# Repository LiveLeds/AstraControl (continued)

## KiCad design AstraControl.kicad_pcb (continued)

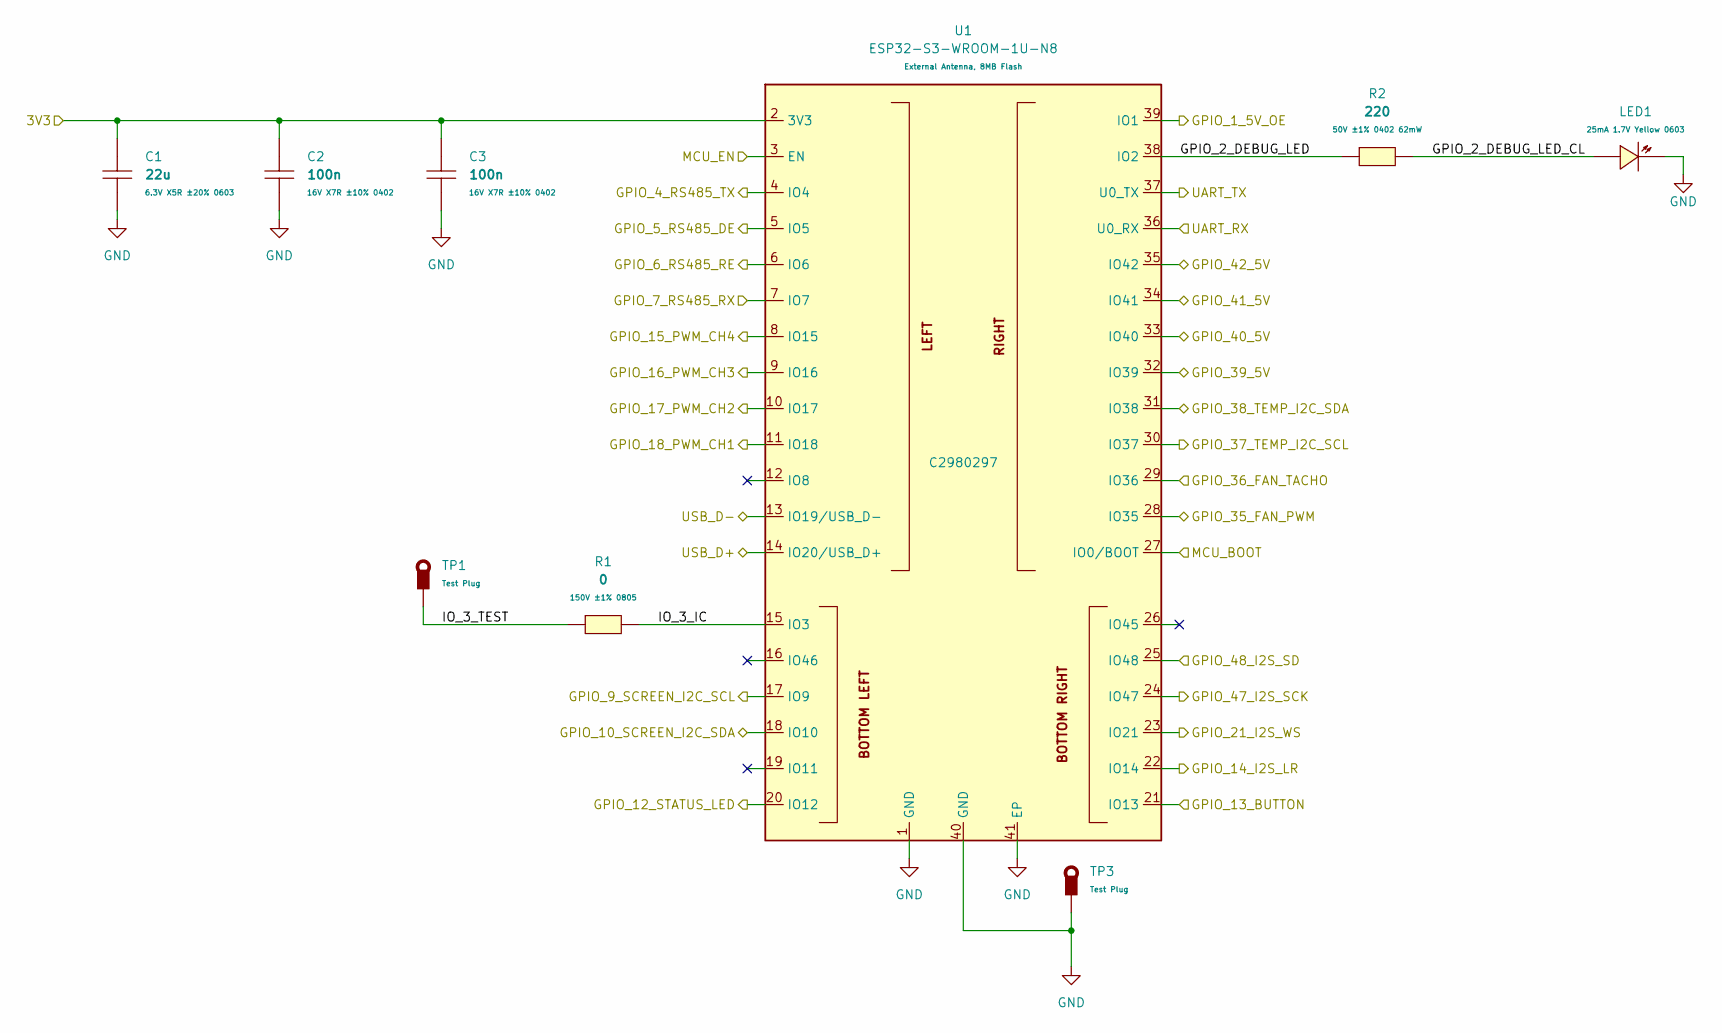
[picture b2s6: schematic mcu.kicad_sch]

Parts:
C1: 22u; C_0603_1608Metric; LCSC Part C59461
C2, C3: 100n; C_0402_1005Metric; LCSC Part C1525
LED1: LED_Yellow_25mA_0603; LED_0603_1608Metric; LCSC Part C72038
R1: 0; R_0805_2012Metric_Pad1.20x1.40mm_HandSolder; LCSC Part C17477
R2: 220; R_0402_1005Metric; LCSC Part C25091
TP1, TP3: TestPoint_Thimble; TestPoint_Loop_D3.50mm_Drill0.9mm_Beaded; LCSC Part C5277086
U1: ESP32-S3-WROOM-1U-N8; WIRELM-SMD_ESP32-S3-WROOM-1U; LCSC Part C2980297

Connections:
+3V3: C1.2, C2.2, C3.2, U1.2 (3V3); also elsewhere on the board
/Block Diagram/3V3 to 5V Logic Shifter/3V3_IO_1: U1.35 (IO42); also elsewhere on the board
/Block Diagram/3V3 to 5V Logic Shifter/3V3_IO_2: U1.34 (IO41); also elsewhere on the board
/Block Diagram/3V3 to 5V Logic Shifter/3V3_IO_3: U1.33 (IO40); also elsewhere on the board
/Block Diagram/3V3 to 5V Logic Shifter/3V3_IO_4: U1.32 (IO39); also elsewhere on the board
/Block Diagram/3V3 to 5V Logic Shifter/LEVEL_SHIFTER_IO_OE: U1.39 (IO1); also elsewhere on the board
/Block Diagram/Button, Status LED, UART and I2S/BUTTON: U1.21 (IO13); also elsewhere on the board
/Block Diagram/Button, Status LED, UART and I2S/I2S_LR: U1.22 (IO14); also elsewhere on the board
/Block Diagram/Button, Status LED, UART and I2S/I2S_SCK: U1.24 (IO47); also elsewhere on the board
/Block Diagram/Button, Status LED, UART and I2S/I2S_SD: U1.25 (IO48); also elsewhere on the board
/Block Diagram/Button, Status LED, UART and I2S/I2S_WS: U1.23 (IO21); also elsewhere on the board
/Block Diagram/Button, Status LED, UART and I2S/STATUS_LED: U1.20 (IO12); also elsewhere on the board
/Block Diagram/Button, Status LED, UART and I2S/UART_RX: U1.36 (U0_RX); also elsewhere on the board
/Block Diagram/Button, Status LED, UART and I2S/UART_TX: U1.37 (U0_TX); also elsewhere on the board
/Block Diagram/Fan, Temperature and Screen/FAN_PWM: U1.28 (IO35); also elsewhere on the board
/Block Diagram/Fan, Temperature and Screen/FAN_TACHO: U1.29 (IO36); also elsewhere on the board
/Block Diagram/Fan, Temperature and Screen/SCREEN_I2C_SCL: U1.17 (IO9); also elsewhere on the board
/Block Diagram/Fan, Temperature and Screen/SCREEN_I2C_SDA: U1.18 (IO10); also elsewhere on the board
/Block Diagram/Fan, Temperature and Screen/TEMP_I2C_SCL: U1.30 (IO37); also elsewhere on the board
/Block Diagram/Fan, Temperature and Screen/TEMP_I2C_SDA: U1.31 (IO38); also elsewhere on the board
/Block Diagram/LED PWM Connector/PWM_CH1: U1.11 (IO18); also elsewhere on the board
/Block Diagram/LED PWM Connector/PWM_CH2: U1.10 (IO17); also elsewhere on the board
/Block Diagram/LED PWM Connector/PWM_CH3: U1.9 (IO16); also elsewhere on the board
/Block Diagram/LED PWM Connector/PWM_CH4: U1.8 (IO15); also elsewhere on the board
/Block Diagram/MCU Enable and Boot/MCU_BOOT: U1.27 (IO0/BOOT); also elsewhere on the board
/Block Diagram/MCU Enable and Boot/MCU_EN: U1.3 (EN); also elsewhere on the board
/Block Diagram/MCU/GPIO_2_DEBUG_LED: R2.1, U1.38 (IO2)
/Block Diagram/MCU/GPIO_2_DEBUG_LED_CL: LED1.2 (A), R2.2
/Block Diagram/MCU/GPIO_4_RS485_TX: U1.4 (IO4); also elsewhere on the board
/Block Diagram/MCU/GPIO_5_RS485_DE: U1.5 (IO5); also elsewhere on the board
/Block Diagram/MCU/GPIO_6_RS485_RE: U1.6 (IO6); also elsewhere on the board
/Block Diagram/MCU/GPIO_7_RS485_RX: U1.7 (IO7); also elsewhere on the board
/Block Diagram/MCU/IO_3_IC: R1.2, U1.15 (IO3)
/Block Diagram/MCU/IO_3_TEST: R1.1, TP1.1
/Block Diagram/MCU/USB_D+: U1.14 (IO20/USB_D+); also elsewhere on the board
/Block Diagram/MCU/USB_D-: U1.13 (IO19/USB_D-); also elsewhere on the board
GND: C1.1, C2.1, C3.1, LED1.1 (K), TP3.1, U1.1 (GND), U1.40 (GND), U1.41 (EP); also elsewhere on the board

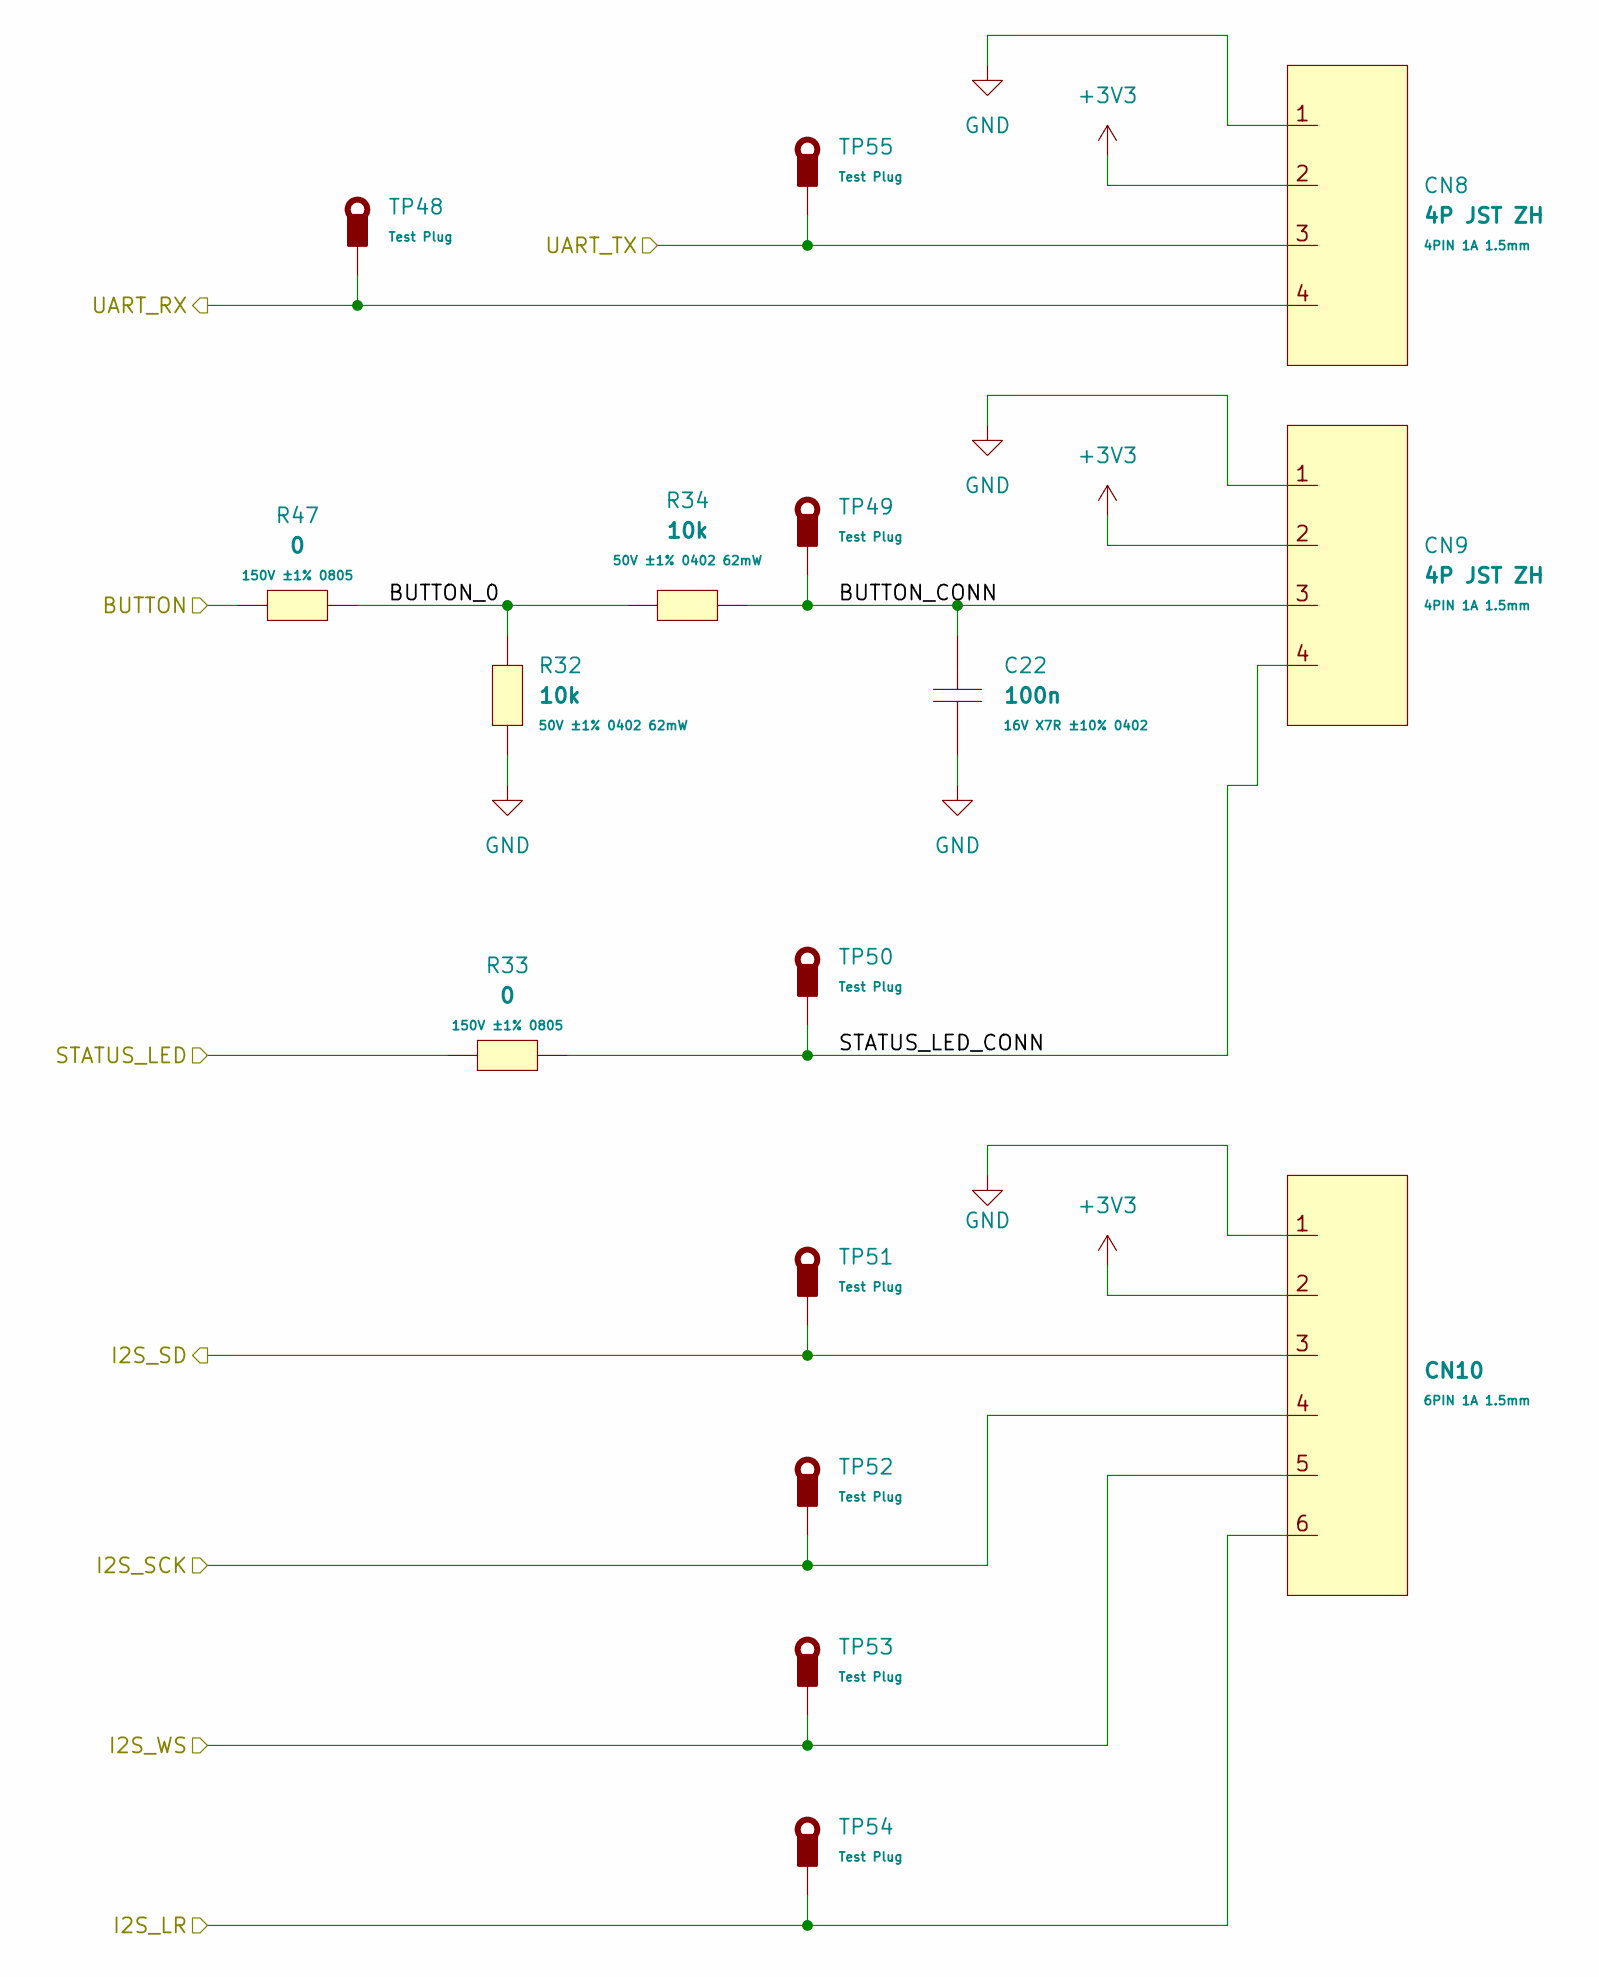
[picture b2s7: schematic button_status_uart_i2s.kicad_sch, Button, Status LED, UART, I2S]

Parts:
C22: 100n; C_0402_1005Metric; LCSC Part C1525
CN8, CN9: 4P JST ZH; JST_ZH_B4B-ZR_1x04_P1.50mm_Vertical; LCSC Part C163034
CN10: JST_ZH_6PIN_1A_250V; JST_ZH_B6B-ZR_1x06_P1.50mm_Vertical; LCSC Part C157984
R32, R34: 10k; R_0402_1005Metric; LCSC Part C25744
R33, R47: 0; R_0805_2012Metric_Pad1.20x1.40mm_HandSolder; LCSC Part C17477
TP48, TP49, TP50, TP51, TP52, TP53, TP54, TP55: TestPoint_Thimble; TestPoint_Loop_D3.50mm_Drill0.9mm_Beaded; LCSC Part C5277086

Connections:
+3V3: CN8.2, CN9.2, CN10.2; also elsewhere on the board
/Block Diagram/Button, Status LED, UART and I2S/BUTTON: R47.1; also elsewhere on the board
/Block Diagram/Button, Status LED, UART and I2S/BUTTON_0: R32.2, R34.2, R47.2
/Block Diagram/Button, Status LED, UART and I2S/BUTTON_CONN: C22.2, CN9.3, R34.1, TP49.1
/Block Diagram/Button, Status LED, UART and I2S/I2S_LR: CN10.6, TP54.1; also elsewhere on the board
/Block Diagram/Button, Status LED, UART and I2S/I2S_SCK: CN10.4, TP52.1; also elsewhere on the board
/Block Diagram/Button, Status LED, UART and I2S/I2S_SD: CN10.3, TP51.1; also elsewhere on the board
/Block Diagram/Button, Status LED, UART and I2S/I2S_WS: CN10.5, TP53.1; also elsewhere on the board
/Block Diagram/Button, Status LED, UART and I2S/STATUS_LED: R33.1; also elsewhere on the board
/Block Diagram/Button, Status LED, UART and I2S/STATUS_LED_CONN: CN9.4, R33.2, TP50.1
/Block Diagram/Button, Status LED, UART and I2S/UART_RX: CN8.4, TP48.1; also elsewhere on the board
/Block Diagram/Button, Status LED, UART and I2S/UART_TX: CN8.3, TP55.1; also elsewhere on the board
GND: C22.1, CN8.1, CN9.1, CN10.1, R32.1; also elsewhere on the board

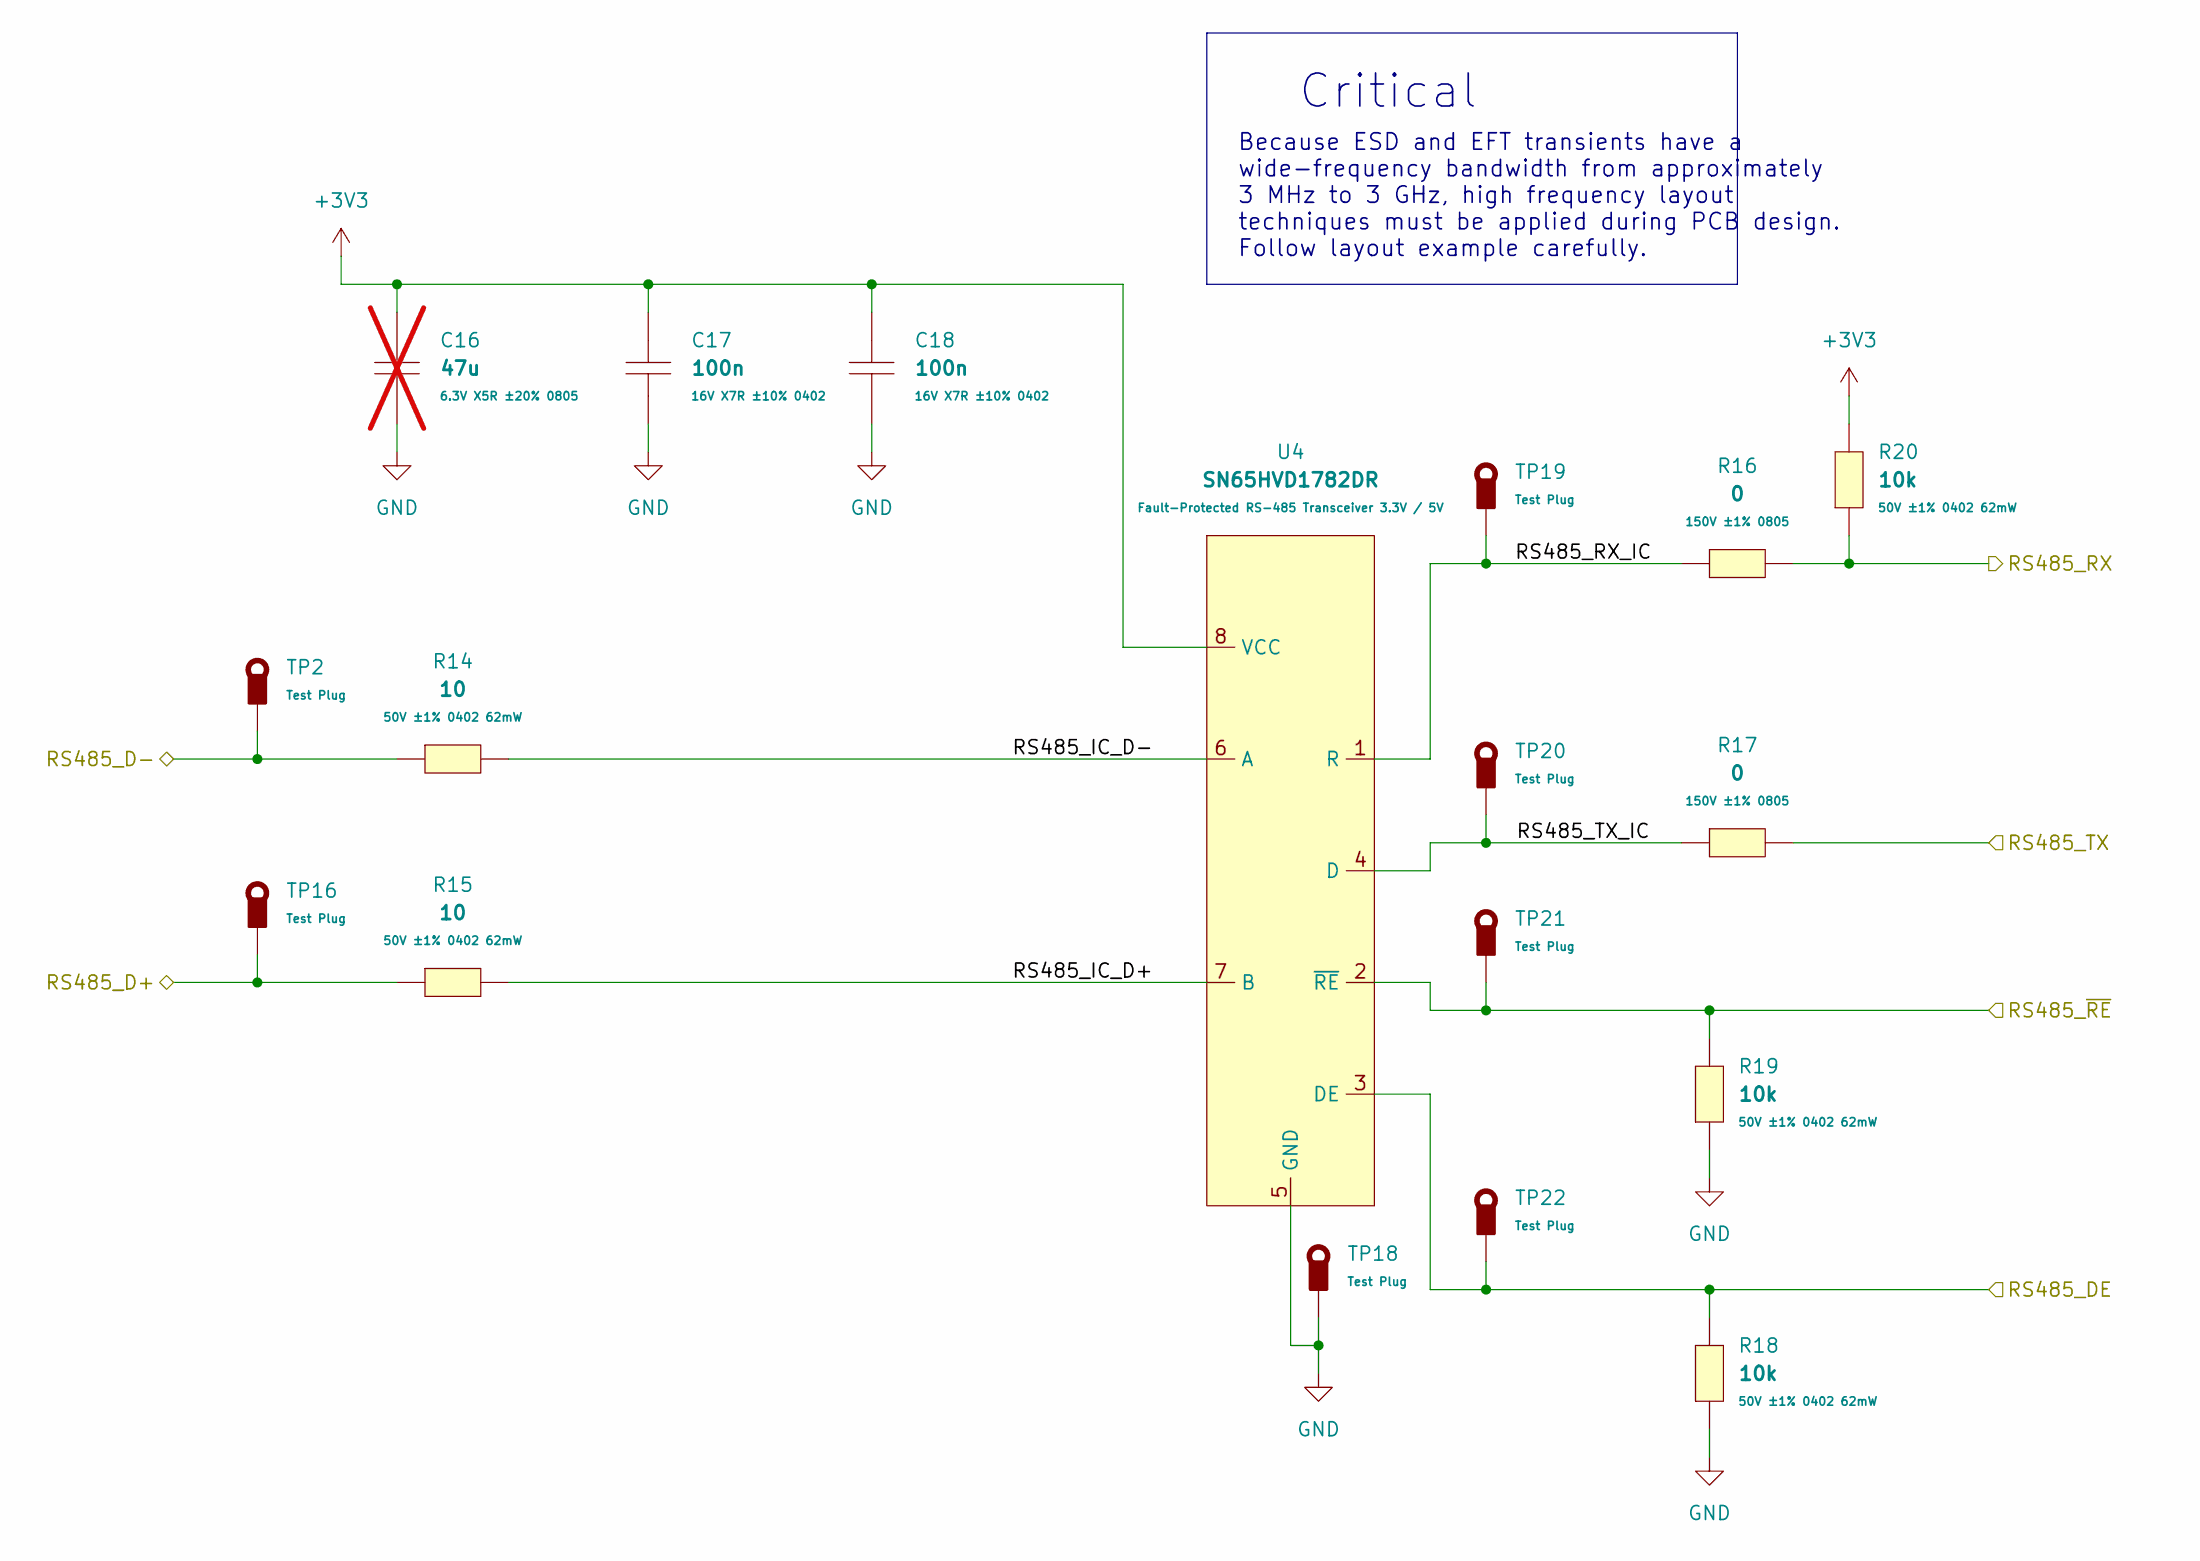
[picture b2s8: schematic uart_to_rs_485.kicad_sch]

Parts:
C16: 47u; C_0805_2012Metric_Pad1.18x1.45mm_HandSolder; LCSC Part C16780; not fitted
C17, C18: 100n; C_0402_1005Metric; LCSC Part C1525
R14, R15: 10; R_0402_1005Metric; LCSC Part C25077
R16, R17: 0; R_0805_2012Metric_Pad1.20x1.40mm_HandSolder; LCSC Part C17477
R18, R19, R20: 10k; R_0402_1005Metric; LCSC Part C25744
TP2, TP16, TP18, TP19, TP20, TP21, TP22: TestPoint_Thimble; TestPoint_Loop_D3.50mm_Drill0.9mm_Beaded; LCSC Part C5277086
U4: SN65HVD1782DR; RS_485_SN65HVD1782DR; LCSC Part C183092

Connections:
+3V3: C16.2, C17.2, C18.2, R20.2, U4.8 (VCC); also elsewhere on the board
/Block Diagram/MCU/GPIO_4_RS485_TX: R17.2; also elsewhere on the board
/Block Diagram/MCU/GPIO_5_RS485_DE: R18.2, TP22.1, U4.3 (DE); also elsewhere on the board
/Block Diagram/MCU/GPIO_6_RS485_RE: R19.2, TP21.1, U4.2 (~RE); also elsewhere on the board
/Block Diagram/MCU/GPIO_7_RS485_RX: R16.2, R20.1; also elsewhere on the board
/Block Diagram/Power Connectors/RS485_D+: R15.1, TP16.1; also elsewhere on the board
/Block Diagram/Power Connectors/RS485_D-: R14.1, TP2.1; also elsewhere on the board
/Block Diagram/UART to RS-485/RS485_IC_D+: R15.2, U4.7 (B)
/Block Diagram/UART to RS-485/RS485_IC_D-: R14.2, U4.6 (A)
/Block Diagram/UART to RS-485/RS485_RX_IC: R16.1, TP19.1, U4.1 (R)
/Block Diagram/UART to RS-485/RS485_TX_IC: R17.1, TP20.1, U4.4 (D)
GND: C16.1, C17.1, C18.1, R18.1, R19.1, TP18.1, U4.5 (GND); also elsewhere on the board

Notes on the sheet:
Because ESD and EFT transients have a wide-frequency bandwidth from approximately 3 MHz to 3 GHz, high frequency layout techniques must be applied during PCB design. Follow layout example carefully.
Critical

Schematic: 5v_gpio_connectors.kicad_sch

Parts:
CN2, CN3: 4P JST VH; JST_VH_B4P-VH-B_1x04_P3.96mm_Vertical; LCSC Part C160317

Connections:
+5V_IN: CN2.2, CN3.2; also elsewhere on the board
/Block Diagram/3V3 to 5V Logic Shifter/5V_IO_1: CN2.3; also elsewhere on the board
/Block Diagram/3V3 to 5V Logic Shifter/5V_IO_2: CN2.4; also elsewhere on the board
/Block Diagram/3V3 to 5V Logic Shifter/5V_IO_3: CN3.3; also elsewhere on the board
/Block Diagram/3V3 to 5V Logic Shifter/5V_IO_4: CN3.4; also elsewhere on the board
GND: CN2.1, CN3.1; also elsewhere on the board

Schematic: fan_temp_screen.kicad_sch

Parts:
C21: 100p; C_0805_2012Metric_Pad1.18x1.45mm_HandSolder; LCSC Part C1790
CN4, CN5, CN6: 4P JST ZH; JST_ZH_B4B-ZR_1x04_P1.50mm_Vertical; LCSC Part C163034
R23, R24, R28, R30: 5k1; R_0402_1005Metric; LCSC Part C25905
R25, R26: 0; R_0805_2012Metric_Pad1.20x1.40mm_HandSolder; LCSC Part C17477
R27: 10k; R_0402_1005Metric; LCSC Part C25744
R29: 3k3; R_0805_2012Metric_Pad1.20x1.40mm_HandSolder; LCSC Part C26010
R43, R44, R45, R46: 0; R_0805_2012Metric_Pad1.20x1.40mm_HandSolder; LCSC Part C17477; not fitted
TP36, TP37, TP38, TP39, TP40, TP41: TestPoint_Thimble; TestPoint_Loop_D3.50mm_Drill0.9mm_Beaded; LCSC Part C5277086

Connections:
+3V3: CN5.2, CN6.2, R23.2, R24.2, R27.2, R28.2, R30.2, R43.2, R44.2, R45.2, R46.2; also elsewhere on the board
+5V_IN: CN4.2; also elsewhere on the board
/Block Diagram/Fan, Temperature and Screen/FAN_PWM: R25.2; also elsewhere on the board
/Block Diagram/Fan, Temperature and Screen/FAN_PWM_CON: CN4.4, R25.1, TP36.1
/Block Diagram/Fan, Temperature and Screen/FAN_TACHO: C21.2, R29.2; also elsewhere on the board
/Block Diagram/Fan, Temperature and Screen/FAN_TACHO_0: R26.2, R27.1, R29.1
/Block Diagram/Fan, Temperature and Screen/FAN_TACHO_CON: CN4.3, R26.1, TP39.1
/Block Diagram/Fan, Temperature and Screen/SCREEN_I2C_SCL: CN6.4, R24.1, R46.1, TP37.1; also elsewhere on the board
/Block Diagram/Fan, Temperature and Screen/SCREEN_I2C_SDA: CN6.3, R28.1, R45.1, TP40.1; also elsewhere on the board
/Block Diagram/Fan, Temperature and Screen/TEMP_I2C_SCL: CN5.4, R23.1, R43.1, TP38.1; also elsewhere on the board
/Block Diagram/Fan, Temperature and Screen/TEMP_I2C_SDA: CN5.3, R30.1, R44.1, TP41.1; also elsewhere on the board
GND: C21.1, CN4.1, CN5.1, CN6.1; also elsewhere on the board

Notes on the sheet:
Cutoff frequency: 482kHz
RC Filter

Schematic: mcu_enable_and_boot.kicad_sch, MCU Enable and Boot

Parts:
C4: 1u; C_0402_1005Metric; LCSC Part C52923
C5, C6: 100n; C_0402_1005Metric; LCSC Part C1525
R3, R5, R6, R7: 0; R_0805_2012Metric_Pad1.20x1.40mm_HandSolder; LCSC Part C17477
R4: 10k; R_0402_1005Metric; LCSC Part C25744
SW1, SW2: TS_Basic_Small; TACTILE_SWITCH-SMD_4P-L5.1-W5.1-P3.70-LS6.5-TL-2; LCSC Part C318884
TP4, TP5: TestPoint_Thimble; TestPoint_Loop_D3.50mm_Drill0.9mm_Beaded; LCSC Part C5277086

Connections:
+3V3: R3.2; also elsewhere on the board
/Block Diagram/MCU Enable and Boot/BOOT_SW: C6.1, R7.2, SW1.2, TP5.1
/Block Diagram/MCU Enable and Boot/EN_DELAY: C4.1, R4.1, R5.2, R6.2
/Block Diagram/MCU Enable and Boot/EN_DELAY_0: R3.1, R4.2
/Block Diagram/MCU Enable and Boot/EN_SW: C5.2, R5.1, SW2.1, TP4.1
/Block Diagram/MCU Enable and Boot/MCU_BOOT: R7.1; also elsewhere on the board
/Block Diagram/MCU Enable and Boot/MCU_EN: R6.1; also elsewhere on the board
GND: C4.2, C5.1, C6.2, SW1.1, SW2.2; also elsewhere on the board

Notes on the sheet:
Information
To ensure that the power supply to the ESP32-S3 chip is stable during power-up, it is advised to add an RC delay circuit at the EN pin.

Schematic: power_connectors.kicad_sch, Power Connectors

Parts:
CN1: 4P JST VH; JST_VH_B4P-VH-B_1x04_P3.96mm_Vertical; LCSC Part C160317
D2, D3: H5VL10B; D_DFN0603_H5VL10B_Bidirectional_TVS; LCSC Part C7420372
TP11, TP12: TestPoint_Thimble; TestPoint_Loop_D3.50mm_Drill0.9mm_Beaded; LCSC Part C5277086

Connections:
+5V_IN: CN1.4; also elsewhere on the board
/Block Diagram/Power Connectors/RS485_D+: CN1.2, D2.2 (A); also elsewhere on the board
/Block Diagram/Power Connectors/RS485_D-: CN1.3, D3.2 (A); also elsewhere on the board
CHASSIS: TP12.1; also elsewhere on the board
GND: CN1.1, D2.1 (C), D3.1 (C), TP11.1; also elsewhere on the board

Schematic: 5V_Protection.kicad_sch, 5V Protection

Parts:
C7, C8: 1u; C_0402_1005Metric; LCSC Part C52923
D1: SS14 Schottky; D_SMA_SS14_C2480; LCSC Part C2480
LED2: LED_RED_20mA_0603; LED_0603_1608Metric; LCSC Part C2286
R8: 220; R_0402_1005Metric; LCSC Part C25091
TP6, TP7: TestPoint_Thimble; TestPoint_Loop_D3.50mm_Drill0.9mm_Beaded; LCSC Part C5277086
U2: NCP361SNT1G; 5V_PROTECTION_NCP361SNT1G_TSOP-5; LCSC Part C233714

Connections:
+5V: C8.1, LED2.2 (A), U2.5 (OUT); also elsewhere on the board
+5V_IN: C7.2, D1.1 (K), TP6.1, U2.1 (IN); also elsewhere on the board
/Block Diagram/5V Protection/5V_PROT_LED: LED2.1 (K), R8.2
/Block Diagram/5V Protection/VBUS: D1.2 (A); also elsewhere on the board
GND: C7.1, C8.2, R8.1, TP7.1, U2.2 (GND), U2.3 (~EN); also elsewhere on the board

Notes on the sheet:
Information
Overvoltage: 5.67V Undervoltage: 3V Max current: 600mA - 780mA Max V_{IN}: 21V

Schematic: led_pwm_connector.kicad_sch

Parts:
CN7: JST_VH_8PIN_10A_250V; JST_VH_B8P-VH-B_1x08_P3.96mm_Vertical; LCSC Part C265117
R31, R39, R40, R41, R42: 0; R_0805_2012Metric_Pad1.20x1.40mm_HandSolder; LCSC Part C17477
TP43, TP44, TP45, TP46, TP47: TestPoint_Thimble; TestPoint_Loop_D3.50mm_Drill0.9mm_Beaded; LCSC Part C5277086

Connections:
+3V3: CN7.7; also elsewhere on the board
+5V_IN: CN7.8; also elsewhere on the board
/Block Diagram/LED PWM Connector/LED_EXTRA_PIN: CN7.1, R31.2, TP46.1
/Block Diagram/LED PWM Connector/PWM_CH1: R41.1; also elsewhere on the board
/Block Diagram/LED PWM Connector/PWM_CH1_CONN: CN7.2, R41.2, TP45.1
/Block Diagram/LED PWM Connector/PWM_CH2: R40.1; also elsewhere on the board
/Block Diagram/LED PWM Connector/PWM_CH2_CONN: CN7.3, R40.2, TP44.1
/Block Diagram/LED PWM Connector/PWM_CH3: R39.1; also elsewhere on the board
/Block Diagram/LED PWM Connector/PWM_CH3_CONN: CN7.4, R39.2, TP43.1
/Block Diagram/LED PWM Connector/PWM_CH4: R42.1; also elsewhere on the board
/Block Diagram/LED PWM Connector/PWM_CH4_CONN: CN7.5, R42.2, TP47.1
GND: CN7.6, R31.1; also elsewhere on the board

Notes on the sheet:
Information
If a different signal is required here the 0Ohm + PTH will allow a post assembly fix / experimentation. Otherwise, just GND.

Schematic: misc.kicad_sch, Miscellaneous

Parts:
C23, C24, C25, C26: 10n; C_0805_2012Metric_Pad1.18x1.45mm_HandSolder; LCSC Part C565682
G1: AstraControl_Ground_Band
R35: 1M; R_0805_2012Metric_Pad1.20x1.40mm_HandSolder; LCSC Part C17514
R36, R37, R38: 1M; R_0805_2012Metric_Pad1.20x1.40mm_HandSolder; LCSC Part C17514; not fitted

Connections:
CHASSIS: C23.2, C24.2, C25.2, C26.2, G1.1 (2), R35.2, R36.2, R37.2, R38.2; also elsewhere on the board
GND: C23.1, C24.1, C25.1, C26.1, R35.1, R36.1, R37.1, R38.1; also elsewhere on the board

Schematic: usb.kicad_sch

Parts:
C27: 100n; C_0402_1005Metric; LCSC Part C1525
R12, R13: 5k1; R_0402_1005Metric; LCSC Part C25905
TP13, TP14, TP15: TestPoint_Thimble; TestPoint_Loop_D3.50mm_Drill0.9mm_Beaded; LCSC Part C5277086
U7: USBLC6-2SC6; USBLC6-2SC6_PROTECTION_SOT-23-6; LCSC Part C7519
USBC1: TYPE-C-31-M-12; USB_C_Korean_Hroparts_Elec_TYPE-C-31-M-12; LCSC Part C165948

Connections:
/Block Diagram/5V Protection/VBUS: C27.2, TP13.1, U7.5 (VBUS), USBC1.A4 (VBUS), USBC1.A9 (VBUS), USBC1.B4 (VBUS), USBC1.B9 (VBUS); also elsewhere on the board
/Block Diagram/MCU/USB_D+: TP15.1, U7.4 (USB_OUT_D+); also elsewhere on the board
/Block Diagram/MCU/USB_D-: TP14.1, U7.6 (USB_OUT_D-); also elsewhere on the board
/Block Diagram/Power Connectors/USB/CC1: R13.2, USBC1.A5 (CC1)
/Block Diagram/Power Connectors/USB/CC2: R12.2, USBC1.B5 (CC2)
/Block Diagram/Power Connectors/USB/USB_CONN_D+: U7.3 (USB_IN_D+), USBC1.A6 (D+), USBC1.B6 (D+)
/Block Diagram/Power Connectors/USB/USB_CONN_D-: U7.1 (USB_IN_D-), USBC1.A7 (D-), USBC1.B7 (D-)
CHASSIS: USBC1.S1 (SHIELD); also elsewhere on the board
GND: C27.1, R12.1, R13.1, U7.2 (GND), USBC1.A1 (GND), USBC1.A12 (GND), USBC1.B1 (GND), USBC1.B12 (GND); also elsewhere on the board

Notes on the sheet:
Route carefully for good performance ESD protection. Place the protection IC as close as possible to the connector.
Critical

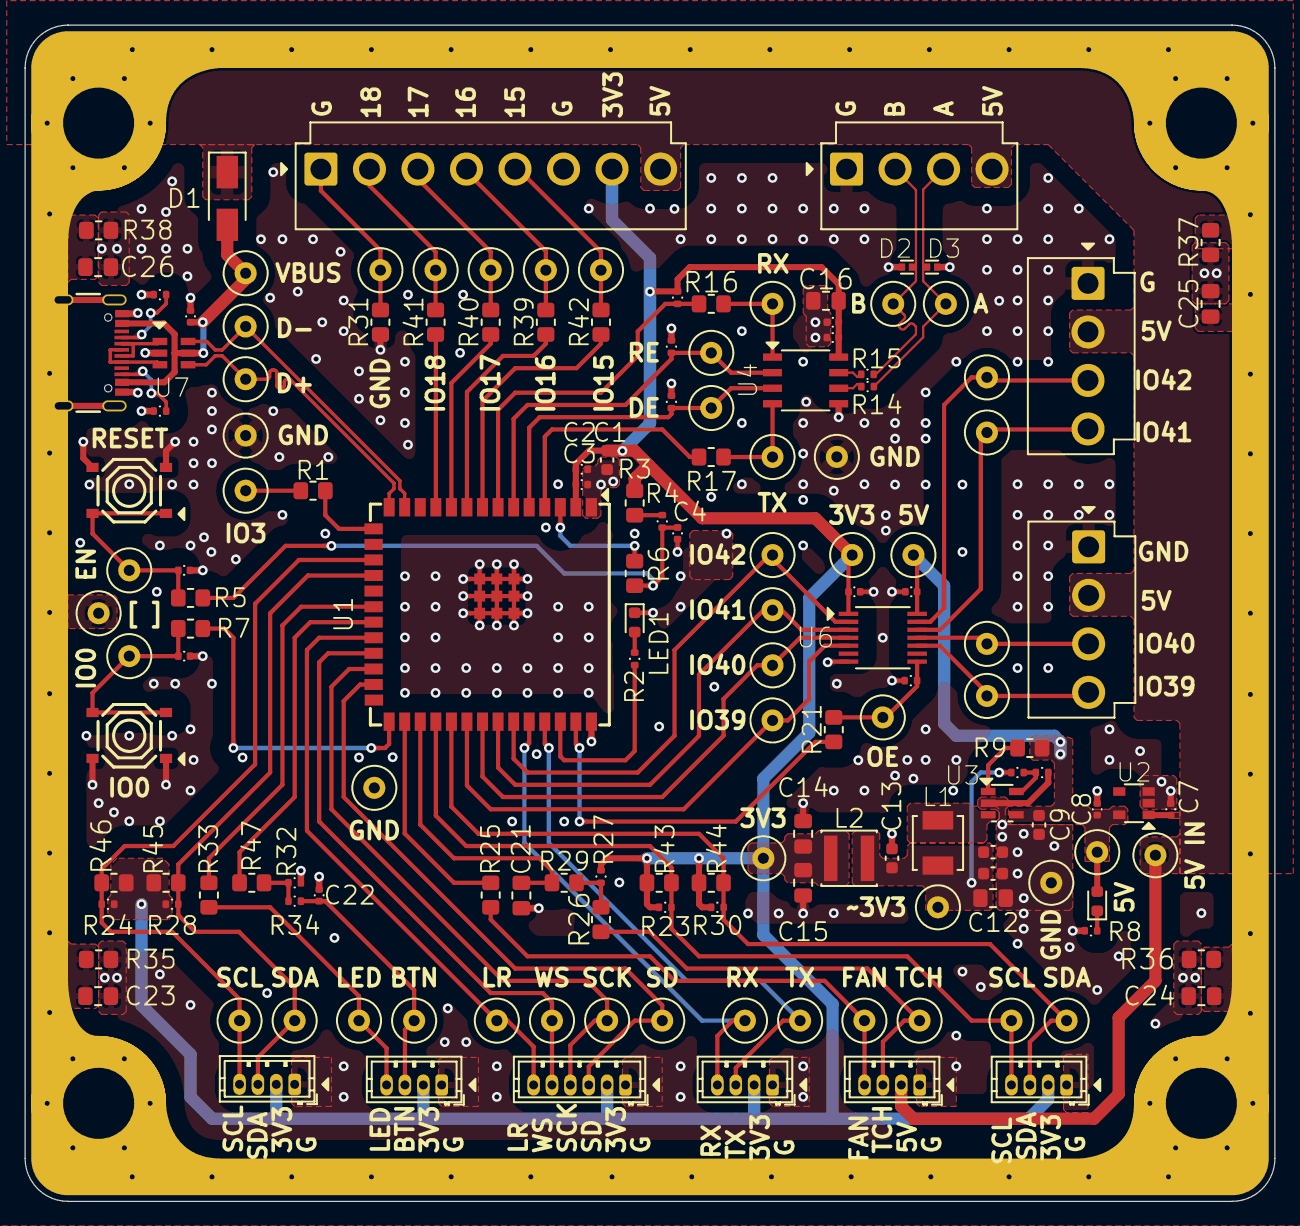
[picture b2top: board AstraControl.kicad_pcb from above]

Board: 4 copper layers, 102.0 x 96.0 mm, 152 parts (0 on the bottom side), 76 nets.

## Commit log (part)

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2024-08-20 workflow
2024-08-20 Use local libs and footprints
2024-08-20 Updated 3d models to local project
2024-08-20 [skip ci] Update repository with generated items
2024-08-21 Added index
2024-08-21 index
2024-08-21 pages
2024-08-22 Added subfolder
2024-08-24 unlock elements
2024-08-24 update elements
2024-08-26 Update wks file
2024-08-26 updated file name
2024-08-26 move template to root
2024-08-26 Try without symlink
2024-08-26 copy as ci step
2024-08-28 Remove plus minus symbol
2024-09-01 Add PCB Print in dark and light colors
2024-09-05 Another redesign
2024-09-06 More routing
2024-09-09 Fixed rs485 for 5v
2024-09-11 RS485 tranceiver changed and TVS
2024-09-21 Reroute complete
2024-09-21 Fixed fab layer
2024-09-21 Silkscreen
2024-09-21 update bottom render, fix center, add gnd pour
2024-09-21 Fix all DRC
2024-09-21 Fixes, added User.1 page
2024-09-21 Add teardrops
2024-09-24 Finished silkscreen
2024-09-24 Text updates, thermal updates
2024-09-29 copper updates
2024-09-29 Set all vias to 08 04
2024-09-29 Fix USB ground ring connection
2024-09-29 remove erc drc
2024-09-29 Improve thermals
2024-09-29 Fix more thermals
2024-09-29 Fix DRC
2024-09-29 Try fix
2024-09-29 Remove colored pads and vias pdf
2024-09-29 Remove pdf merge
2024-09-29 Fixing JLCPCB FDM
2024-09-29 More fdm fixes
2024-09-29 Preflight crash
2024-09-29 Fix alignment of pcb parts
2024-09-30 Added MFN MPR to each components for eurocircuits
2024-09-30 Fixed CI copy, added KiRi
2024-09-30 Set kiri max commits to 3
2024-09-30 Updated index.md
2024-09-30 Updated KiRi
2024-09-30 Fix kiri missing dir
2024-09-30 Fix build
2024-10-01 Fix origin for cpl
2024-10-01 Cleanup
2024-10-05 Migrate library to submodule
2024-10-05 Fix kiri
2024-10-05 Allow kiri to git clone
2024-10-05 use https for submodule
2024-10-05 Updated submodule
2024-10-05 removed library
2024-10-05 Add library
2024-10-05 Allow kiri submodule clone
2024-10-06 Use SSH private key
2024-10-06 Added deploy key
2024-10-06 Move key adding to right step
2024-10-06 Updated key
2024-10-06 Try add github hosts to known hosts
2024-10-06 Added jq
2024-10-06 Try remove private key stuff
2024-10-06 print known hosts and restart ssh
2024-10-06 More testing
2024-10-06 New approach
2024-10-06 attempt
2024-10-06 Try again
2024-10-06 Different add
2024-10-06 fix for github
2024-10-06 Add known hosts key
2024-10-06 Try2
2024-10-06 Remove print
2024-10-06 Try fix known hosts in docker
2024-10-06 Use different redir
2024-10-06 Check KiRi
2024-10-06 Test
2024-10-06 Fix ssh dir
2024-10-06 Fix urls
2024-10-06 Updated footprint model path
2024-10-06 Update schematic titles, templates
2024-10-08 Minor updates
2024-10-08 Add more prints
2024-10-08 Set future true
2024-10-08 Minor change
2024-10-08 Add extra step for KiRi
2024-10-08 Kiriiiiii
2024-10-08 Update owner
2024-10-08 Update to copy
2024-10-11 Updated Pi filter
2024-11-13 Update connector
2024-11-13 Skip kiri failures
2024-11-13 Add step update top angled
2024-11-13 Added step link, reverted 3d angled top
2024-11-23 updated render
2024-11-23 HQ render
2024-11-24 Prepare for review, silkscreen updates, minor tweaks
2024-11-24 ci and homepage updates
2024-11-24 Fix Gerberviewer
2024-11-24 Added last commit
2024-11-24 Fix fab, 100 samples
2024-11-29 Flip IN silkscreen
2024-12-01 Fix gnd on jst pins
2024-12-08 Update to new rs485 chip, use 2 bit 5v gpio
2024-12-08 Finished cleanup
2024-12-08 Updated USB chassis connection
2024-12-08 Fab and cleanup
2024-12-08 Fix silkscreen gpio 5v name
2024-12-09 New inductor that is in stock, updated rs485 ic layout to put caps closer
2024-12-10 Tweaks for JLC
2024-12-10 JLC tweaks
2024-12-10 Fixed 1 odd via, fixed gnd via symmetry
2024-12-10 JLC fixes
2024-12-11 Minor fixes
2024-12-11 Try to fix config
2024-12-11 Fix filter
2024-12-13 Fix USB for jlc
2024-12-13 Tweaks
2024-12-13 GND tweak
2024-12-13 Tweak
2024-12-15 Fix silkscreen on copper, add GPIO 8 to connector
2024-12-15 updated lib
2024-12-26 Updated to JST SH, 3A diode for USB, added extra 2P VH
2024-12-27 Fix yaml
2024-12-29 Update fan to rpi style pinout, minor cosmetic fixes
2025-01-07 Minor tweaks
2025-01-07 Updated thermal vias
2025-01-07 index.md update
2025-01-10 Tweaks, cleanup, reference images in schematic
2025-01-10 Try different color finishes
2025-01-10 Update revision and add year to silkscreen
2025-01-10 red mask
2025-01-10 tweak render settings
2025-01-10 Tweak render
2025-01-10 Render purple HQ
2025-01-13 Fix for JLC DFM
2025-01-14 HD render
2025-01-14 Minor cleanup
2025-01-14 index updates
2025-01-15 Minor fix for shifter gnd
2025-01-18 Schematic cleanup
2025-01-20 Swap to ESP 32 S3 N16 for availability
2025-01-20 3 samples renders
2025-01-20 Use alternative sh 6 pin that is in stock
2025-01-23 Revert to normal jst connector without solder retention cup
2025-01-28 Updated resistors for leds, added more back silkscreen
2025-01-29 update drc html
2025-01-29 updated 6 pin connector
2025-01-29 Board cleanup and updates
2025-01-29 fix thermal pad
2025-04-01 Minor improvements to layout
2025-04-01 Increase clearance between non TP PTH and vias
2025-04-01 Back to enig and black
2025-04-01 Updated VH 8 PIN to clone
2025-04-01 Fix 3d
2025-04-01 Bring back teardrops
2025-04-04 Updated zone connection for themal vias
